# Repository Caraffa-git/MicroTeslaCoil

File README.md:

# μTeslaCoil
Small PCB for push-pull tesla coil with 50V boost converter

## Notes and test results (<a href="https://github.com/Caraffa-git/MicroTeslaCoil/tree/b3fdc67581c9563461222aec662bbb1328c567a8">b3fdc67</a>)
The coil works, but aside from some not-so-wise design decisions that I changed in the current version, I encountered a few problems.
- At first the idea was to use a slayer-exciter sized secondary but as it turned out driving a coil with a frequency close to 5MHz can be challenging in terms of tuning. I ended up using a slightly larger secondary with a resonance frequency close to 500-600kHz.
- The lack of TVS diodes cost me some IGBTs so I added them in this version. As it turns out, reverse connection of the primary winding causes high voltage spikes and thus damage to the circuit.
- The voltage converter that I used has a limit of ~60V on the output, but there is some headroom so you can experiment with higher voltages. I think the circuit should be able to withstand about 80V on the input.

<!-- |   |   |   |
|---|---|---|
|  | | | -->

<!--  -->

## TODO
- Add Q3 gate protection
- Add U2 VCC regulation/protection 

## Links
https://www.youtube.com/watch?v=w9AY5RUtEMk   
https://tefatronix.g6.cz/display.php?page=sstc4&lang=en   
~~https://blog.naver.com/3happy3gong3/222702706706~~   
https://github.com/Caraffa-git/PCB-Art

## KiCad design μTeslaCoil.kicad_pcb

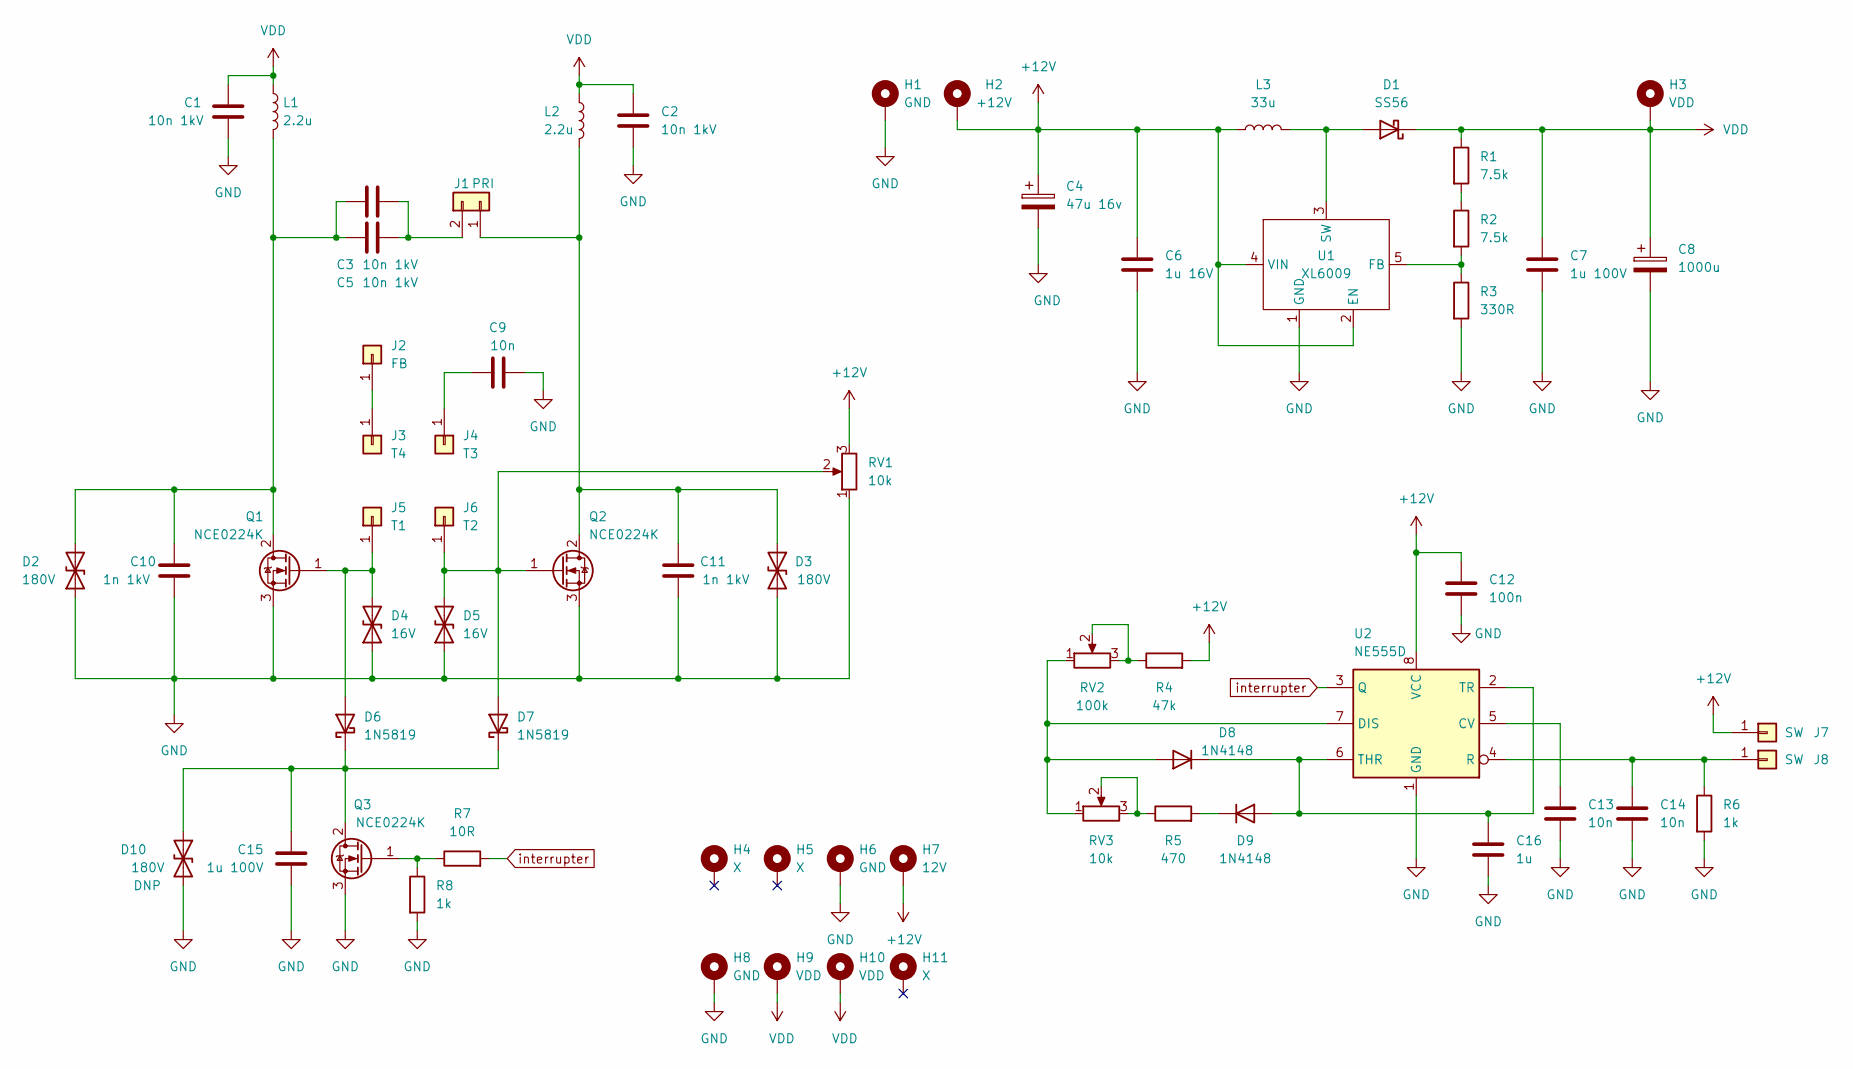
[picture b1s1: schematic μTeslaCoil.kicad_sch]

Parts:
C1, C2, C3, C5: 10n 1kV; C_1206_3216Metric
C4: 47u 16v; CP_Radial_D4.0mm_P1.50mm
C6: 1u 16V; C_0805_2012Metric
C7, C15: 1u 100V; C_1206_3216Metric
C8: 1000u; CP_Radial_D16.0mm_P7.50mm
C9: 10n; C_1206_3216Metric
C10, C11: 1n 1kV; C_1206_3216Metric
C12: 100n; C_0805_2012Metric
C13, C14: 10n; C_0805_2012Metric
C16: 1u; C_0805_2012Metric
D1: SS56; D_SMC
D2, D3, D10: 180V; D_SMB
D4, D5: 16V; D_SMB
D6, D7: 1N5819; D_SOD-123
D8, D9: 1N4148; D_SOD-123
H1, H6, H8: GND; MountingHole_2.2mm_M2_DIN965_Pad
H2: +12V; MountingHole_2.2mm_M2_DIN965_Pad
H3, H9, H10: VDD; MountingHole_2.2mm_M2_DIN965_Pad
H4, H5, H11: X; MountingHole_2.2mm_M2_DIN965_Pad
H7: 12V; MountingHole_2.2mm_M2_DIN965_Pad
J1: PRI; TerminalBlock_bornier-2_P5.08mm
J2: FB
J3: T4
J4: T3; TestPoint_Pad_1.0x1.0mm
J5: T1; TestPoint_Pad_1.0x1.0mm
J6: T2; TestPoint_Pad_1.0x1.0mm
J7, J8: SW; TestPoint_Pad_1.0x1.0mm
L1, L2: 2.2u; L 6.6x7.1
L3: 33u; L 6.6x7.3
Q1, Q2, Q3: NCE0224K; TO-252-2
R1, R2: 7.5k; R_0805_2012Metric
R3: 330R; R_0805_2012Metric
R4: 47k; R_0805_2012Metric
R5: 470; R_0805_2012Metric
R6, R8: 1k; R_0805_2012Metric
R7: 10R; R_0805_2012Metric
RV1: 10k; Potentiometer_Bourns_3296W_Vertical
RV2: 100k; Potentiometer_ACP_CA9-H2,5_Horizontal
RV3: 10k; Potentiometer_ACP_CA9-H2,5_Horizontal
U1: XL6009; TO-263-5_TabPin3
U2: NE555D; SOIC-8_3.9x4.9mm_P1.27mm

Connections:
+12V: C4.1, C6.1, C12.1, H2.1, H7.1, J7.1, L3.1, R4.2, RV1.3, U1.2 (EN), U1.4 (VIN), U2.8 (VCC)
GND: C1.2, C2.2, C4.2, C6.2, C7.2, C8.2, C9.2, C10.2, C11.2, C12.2, C13.2, C14.2, C15.2, C16.2, D2.1 (A1), D3.2 (A2), D4.1 (A1), D5.1 (A1), D10.2 (A2), H1.1, H6.1, H8.1, Q1.3 (S), Q2.3 (S), Q3.3 (S), R3.2, R6.2, R8.2, RV1.1, U1.1 (GND), U2.1 (GND)
unnamed: C3.2, C5.2, J1.2
unnamed: C9.1, J4.1
unnamed: C3.1, C5.1, C10.1, D2.2 (A2), L1.2, Q1.2 (D)
unnamed: C11.1, D3.1 (A1), J1.1, L2.2, Q2.2 (D)
unnamed: C13.1, U2.5 (CV)
unnamed: C14.1, J8.1, R6.1, U2.4 (R)
unnamed: C15.1, D6.1 (K), D7.1 (K), D10.1 (A1), Q3.2 (D)
unnamed: C16.1, D8.1 (K), D9.2 (A), U2.2 (TR), U2.6 (THR)
unnamed: D1.2 (A), L3.2, U1.3 (SW)
unnamed: D4.2 (A2), D6.2 (A), J5.1, Q1.1 (G)
unnamed: D5.2 (A2), D7.2 (A), J6.1, Q2.1 (G), RV1.2
unnamed: D8.2 (A), RV2.1, RV3.1, U2.7 (DIS)
unnamed: D9.1 (K), R5.2
unnamed: J2.1, J3.1
unnamed: Q3.1 (G), R7.1, R8.1
unnamed: R1.2, R2.1
unnamed: R2.2, R3.1, U1.5 (FB)
unnamed: R4.1, RV2.2, RV2.3
unnamed: R5.1, RV3.2, RV3.3
VDD: C1.1, C2.1, C7.1, C8.1, D1.1 (K), H3.1, H9.1, H10.1, L1.1, L2.1, R1.1
interrupter: R7.2, U2.3 (Q)

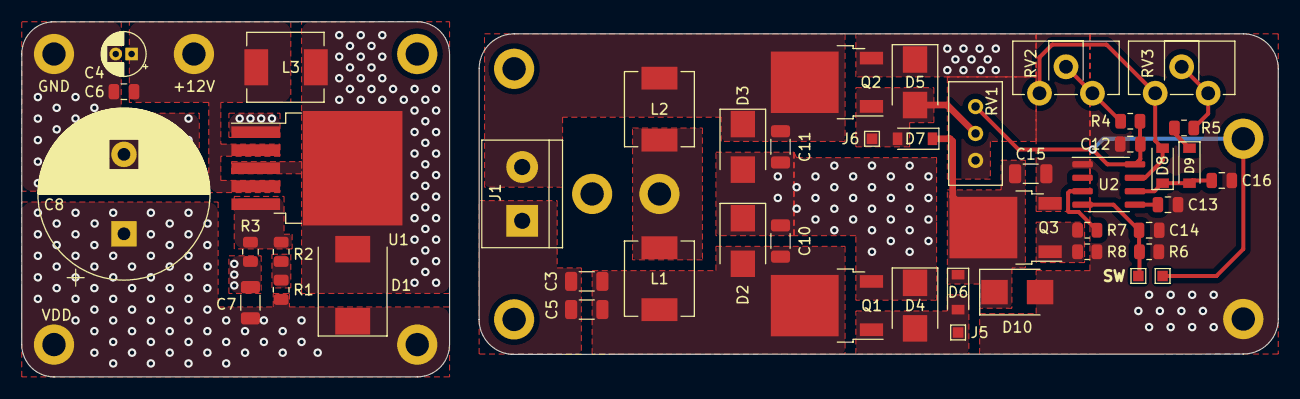
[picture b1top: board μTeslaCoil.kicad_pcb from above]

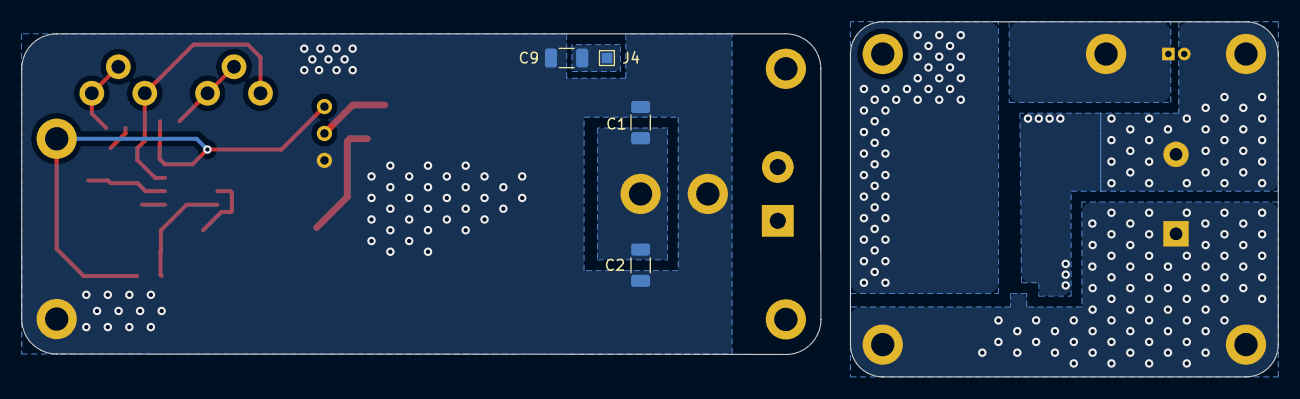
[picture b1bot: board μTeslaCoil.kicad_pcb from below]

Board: 2 copper layers, 118.6 x 33.5 mm, 62 parts (4 on the bottom side), 22 nets.

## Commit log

2023-02-18 small clean-up
2023-02-18 git ignore
2023-02-18 schematic
2023-02-18 images
2023-07-01 updated PCB view
2023-07-01 schematic update
2023-07-01 new pictures
2023-07-01 rev 1.3
2023-07-01 updated schematic
2023-07-01 updated BOM
2024-08-17 final clean-up
